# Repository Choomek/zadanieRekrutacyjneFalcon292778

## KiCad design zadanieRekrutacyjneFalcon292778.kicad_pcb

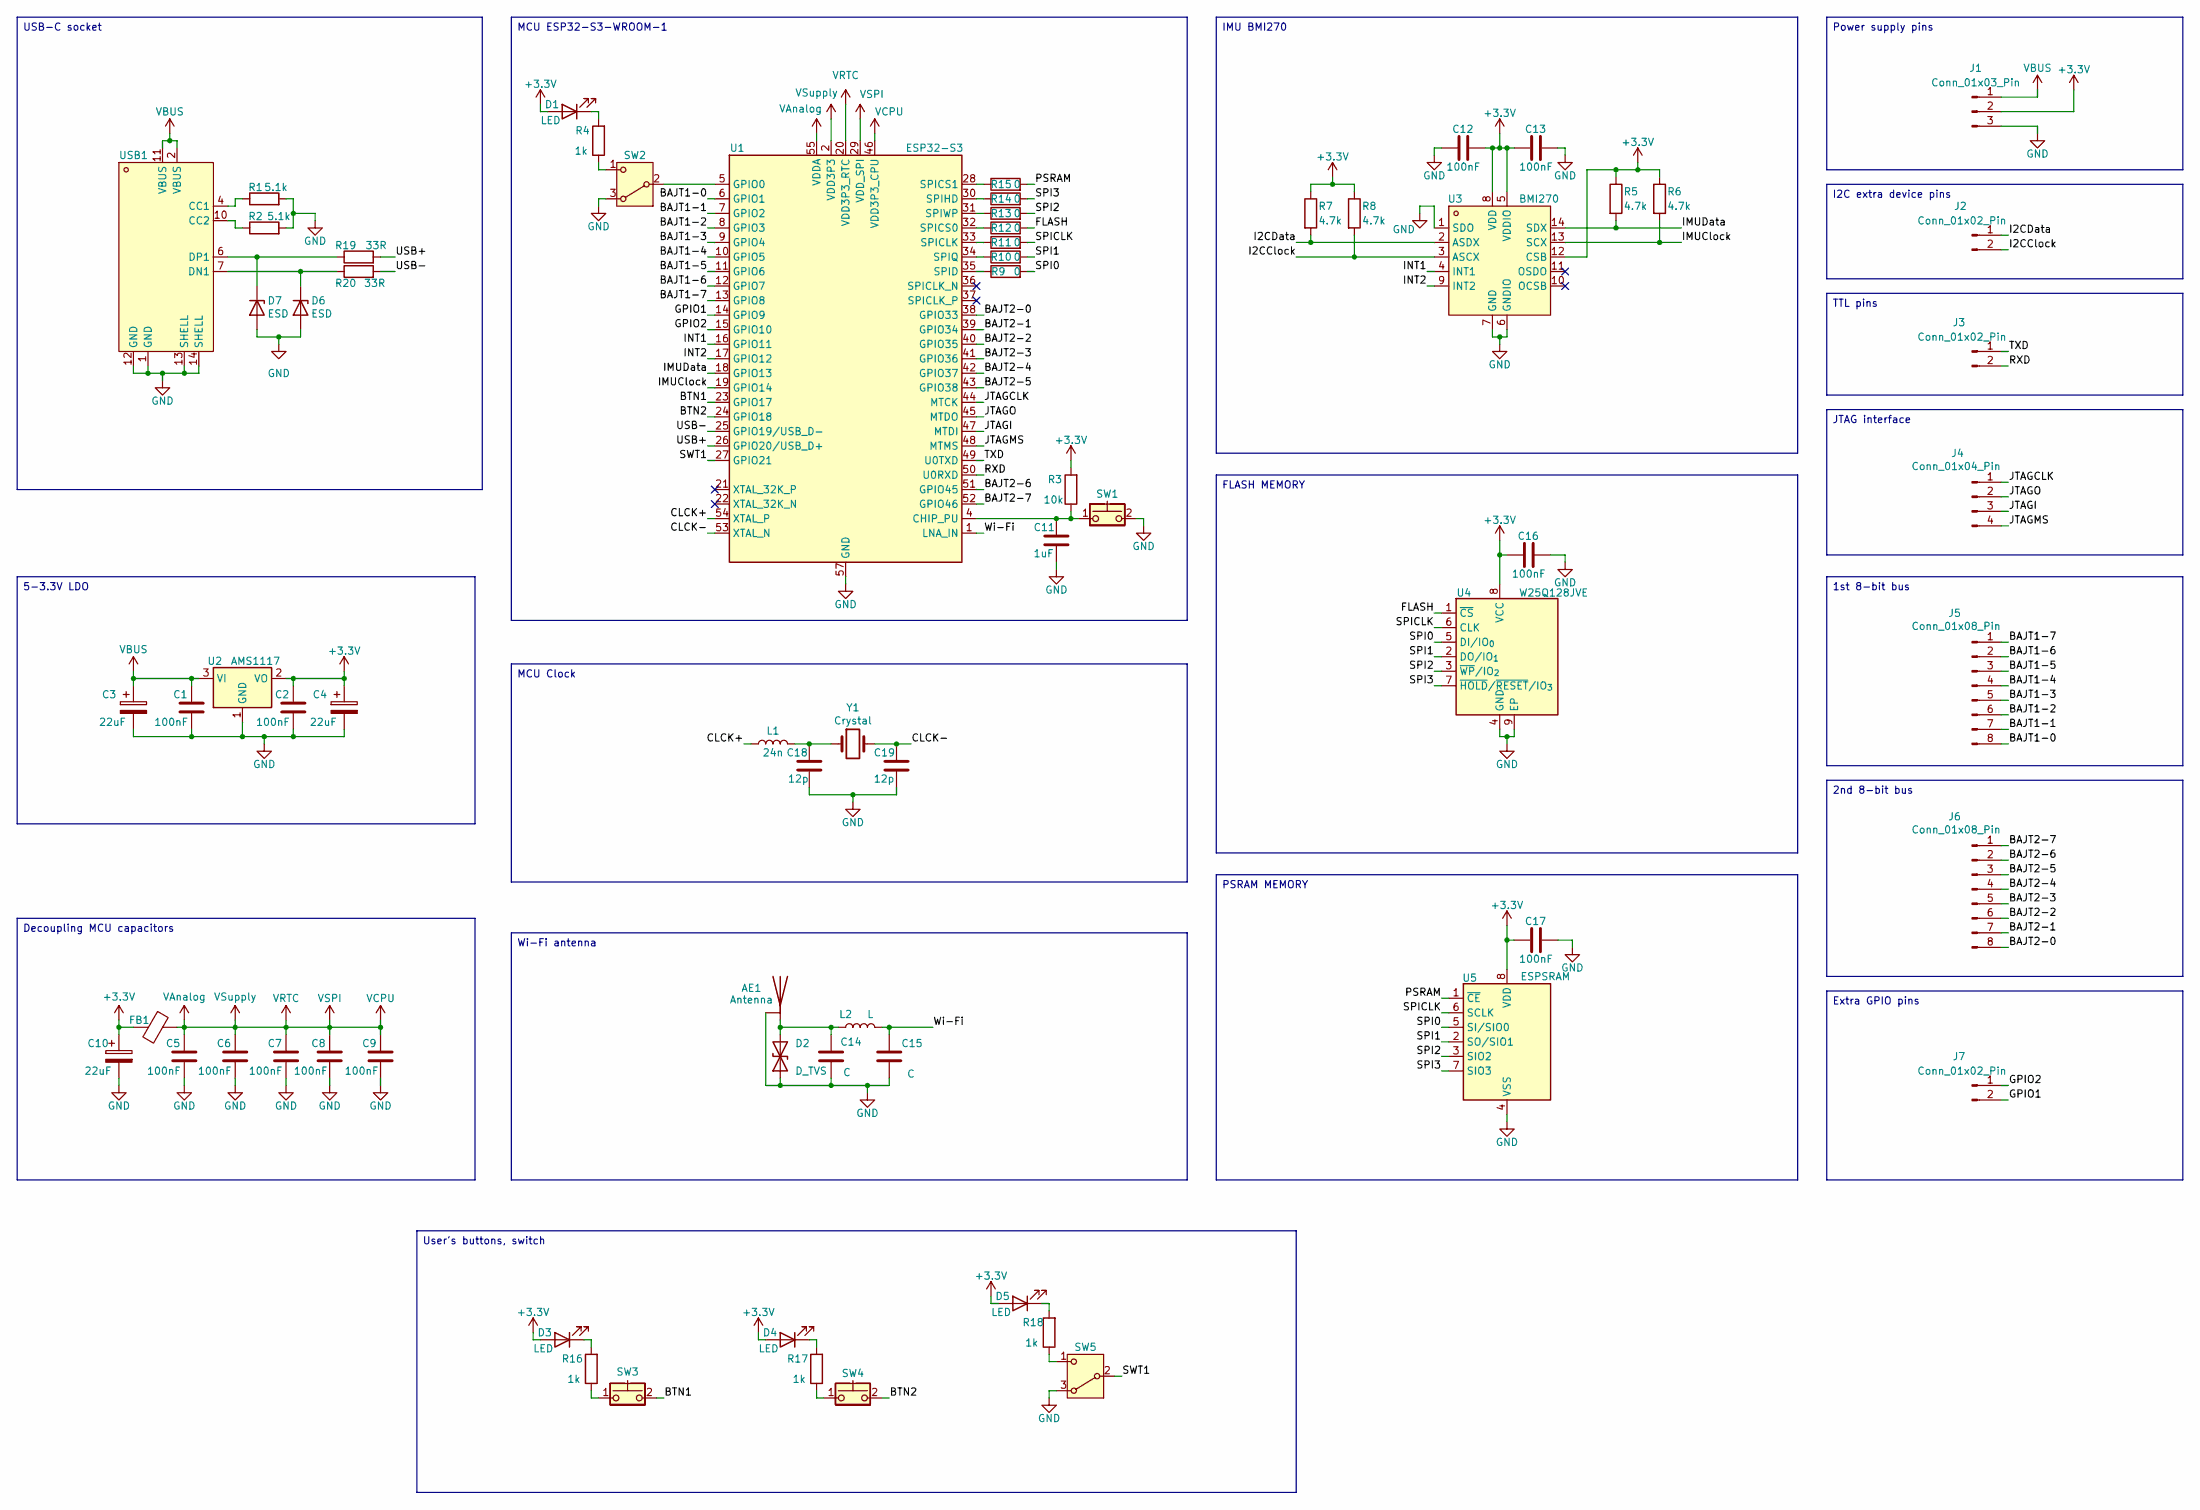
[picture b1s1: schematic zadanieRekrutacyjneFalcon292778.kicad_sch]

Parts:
AE1: Antenna; Texas_SWRA117D_2.4GHz_Right
C1, C2, C5, C6, C7, C8, C9, C12, C13, C16, C17: 100nF; C_0603_1608Metric
C3, C4, C10: 22uF; CP_Axial_L11.0mm_D5.0mm_P18.00mm_Horizontal
C11: 1uF; C_0603_1608Metric
C14, C15: C; C_0603_1608Metric
C18, C19: 12p; C_0603_1608Metric
D1, D3, D4, D5: LED; LED_0603_1608Metric
D2: D_TVS; Texas_DPY0002A_0.6x1mm_P0.65mm
D6, D7: ESD; D_SOD-523
FB1: FerriteBead; LairdTech_28C0236-0JW-10
J1: Conn_01x03_Pin; PinHeader_1x03_P2.54mm_Vertical
J2, J3, J7: Conn_01x02_Pin; PinHeader_1x02_P2.54mm_Vertical
J4: Conn_01x04_Pin; PinHeader_1x04_P2.54mm_Vertical
J5, J6: Conn_01x08_Pin; PinHeader_1x08_P2.54mm_Vertical
L1: 24n; L_0603_1608Metric
L2: L; L_0603_1608Metric
R1, R2: 5.1k; R_0603_1608Metric
R3: 10k; R_0603_1608Metric
R4, R16, R17, R18: 1k; R_0603_1608Metric
R5, R6, R7, R8: 4.7k; R_0603_1608Metric
R9, R10, R11, R12, R13, R14, R15: 0; R_0603_1608Metric
R19, R20: 33R; R_0603_1608Metric
SW1, SW3, SW4: CK_KMS2xxG; SW_SPST_CK_KMS2xxGP
SW2, SW5: SW_Nidec_CAS-120A1; Nidec_Copal_CAS-120A
U1: ESP32-S3; QFN-56-1EP_7x7mm_P0.4mm_EP4x4mm
U2: AMS1117; SOT-223-3_TabPin2
U3: BMI270; LGA-14_L3.0-W2.5-P0.50-BR; LCSC Part C2836813
U4: W25Q128JVE; WSON-8-1EP_8x6mm_P1.27mm_EP3.4x4.3mm
U5: ESPSRAM; SOIC-8_3.9x4.9mm_P1.27mm
USB1: TYPE-C 16PIN 2MD(073); USB-C-SMD_TYPE-C-6PIN-2MD-073; LCSC Part C2765186
Y1: Crystal; Resonator-2Pin_W7.0mm_H2.5mm

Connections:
+3.3V: C2.1, C4.1, C10.1, C12.1, C13.2, C16.2, C17.2, D1.2 (A), D3.2 (A), D4.2 (A), D5.2 (A), FB1.2, J1.2, R3.2, R5.1, R6.1, R7.1, R8.1, U2.2 (VO), U3.5 (VDDIO), U3.8 (VDD), U3.12 (CSB), U4.8 (VCC), U5.8 (VDD)
/BAJT1-0: J5.8, U1.6 (GPIO1)
/BAJT1-1: J5.7, U1.7 (GPIO2)
/BAJT1-2: J5.6, U1.8 (GPIO3)
/BAJT1-3: J5.5, U1.9 (GPIO4)
/BAJT1-4: J5.4, U1.10 (GPIO5)
/BAJT1-5: J5.3, U1.11 (GPIO6)
/BAJT1-6: J5.2, U1.12 (GPIO7)
/BAJT1-7: J5.1, U1.13 (GPIO8)
/BAJT2-0: J6.8, U1.38 (GPIO33)
/BAJT2-1: J6.7, U1.39 (GPIO34)
/BAJT2-2: J6.6, U1.40 (GPIO35)
/BAJT2-3: J6.5, U1.41 (GPIO36)
/BAJT2-4: J6.4, U1.42 (GPIO37)
/BAJT2-5: J6.3, U1.43 (GPIO38)
/BAJT2-6: J6.2, U1.51 (GPIO45)
/BAJT2-7: J6.1, U1.52 (GPIO46)
/BTN1: SW3.2, U1.23 (GPIO17)
/BTN2: SW4.2, U1.24 (GPIO18)
/CLCK+: L1.1, U1.54 (XTAL_P)
/CLCK-: C19.1, U1.53 (XTAL_N), Y1.2
/FLASH: R12.2, U4.1 (~CS)
/GPIO1: J7.2, U1.14 (GPIO9)
/GPIO2: J7.1, U1.15 (GPIO10)
/I2CClock: J2.2, R8.2, U3.3 (ASCX)
/I2CData: J2.1, R7.2, U3.2 (ASDX)
/IMUClock: R6.2, U1.19 (GPIO14), U3.13 (SCX)
/IMUData: R5.2, U1.18 (GPIO13), U3.14 (SDX)
/INT1: U1.16 (GPIO11), U3.4 (INT1)
/INT2: U1.17 (GPIO12), U3.9 (INT2)
/JTAGCLK: J4.1, U1.44 (MTCK)
/JTAGI: J4.3, U1.47 (MTDI)
/JTAGMS: J4.4, U1.48 (MTMS)
/JTAGO: J4.2, U1.45 (MTDO)
/PSRAM: R15.2, U5.1 (~CE)
/RXD: J3.2, U1.50 (U0RXD)
/SPI0: R9.2, U4.5 (DI/IO_{0}), U5.5 (SI/SIO0)
/SPI1: R10.2, U4.2 (DO/IO_{1}), U5.2 (SO/SIO1)
/SPI2: R13.2, U4.3 (~WP/IO_{2}), U5.3 (SIO2)
/SPI3: R14.2, U4.7 (~HOLD/~RESET/IO_{3}), U5.7 (SIO3)
/SPICLK: R11.2, U4.6 (CLK), U5.6 (SCLK)
/SWT1: SW5.2 (B), U1.27 (GPIO21)
/TXD: J3.1, U1.49 (U0TXD)
/USB+: R19.2, U1.26 (GPIO20/USB_D+)
/USB-: R20.2, U1.25 (GPIO19/USB_D-)
/Wi-Fi: C15.1, L2.2, U1.1 (LNA_IN)
GND: AE1.2 (GND), C1.2, C2.2, C3.2, C4.2, C5.2, C6.2, C7.2, C8.2, C9.2, C10.2, C11.2, C12.2, C13.1, C14.2, C15.2, C16.1, C17.1, C18.2, C19.2, D2.1 (A1), D6.2 (A), D7.2 (A), J1.3, R1.2, R2.2, SW1.2, SW2.3 (A), SW5.3 (A), U1.57 (GND), U2.1 (GND), U3.1 (SDO), U3.6 (GNDIO), U3.7 (GND), U4.4 (GND), U4.9 (EP), U5.4 (VSS), USB1.1 (GND), USB1.12 (GND), USB1.13 (SHELL), USB1.14 (SHELL)
unnamed: AE1.1 (A), C14.1, D2.2 (A2), L2.1
unnamed: C18.1, L1.2, Y1.1
unnamed: D1.1 (K), R4.2
unnamed: D3.1 (K), R16.2
unnamed: D4.1 (K), R17.2
unnamed: D5.1 (K), R18.2
unnamed: D6.1 (K), R20.1, USB1.7 (DN1)
unnamed: D7.1 (K), R19.1, USB1.6 (DP1)
unnamed: R16.1, SW3.1
unnamed: R17.1, SW4.1
unnamed: SW2.2 (B), U1.5 (GPIO0)
unnamed: R4.1, SW2.1 (C)
unnamed: R18.1, SW5.1 (C)
unnamed: C11.1, R3.1, SW1.1, U1.4 (CHIP_PU)
unnamed: R11.1, U1.33 (SPICLK)
unnamed: R12.1, U1.32 (SPICS0)
unnamed: R15.1, U1.28 (SPICS1)
unnamed: R9.1, U1.35 (SPID)
unnamed: R14.1, U1.30 (SPIHD)
unnamed: R10.1, U1.34 (SPIQ)
unnamed: R13.1, U1.31 (SPIWP)
unnamed: R1.1, USB1.4 (CC1)
unnamed: R2.1, USB1.10 (CC2)
VAnalog: C5.1, C6.1, C7.1, C8.1, C9.1, FB1.1, U1.2 (VDD3P3), U1.3 (VDD3P3), U1.20 (VDD3P3_RTC), U1.29 (VDD_SPI), U1.46 (VDD3P3_CPU), U1.55 (VDDA), U1.56 (VDDA)
VBUS: C1.1, C3.1, J1.1, U2.3 (VI), USB1.2 (VBUS), USB1.11 (VBUS)

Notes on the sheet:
2nd 8-bit bus
Wi-Fi antenna
IMU BMI270
Decoupling MCU capacitors
USB-C socket
TTL pins
MCU ESP32-S3-WROOM-1
Power supply pins
1st 8-bit bus
PSRAM MEMORY
5-3.3V LDO
FLASH MEMORY
JTAG interface
Extra GPIO pins
User's buttons, switch
I2C extra device pins
MCU Clock

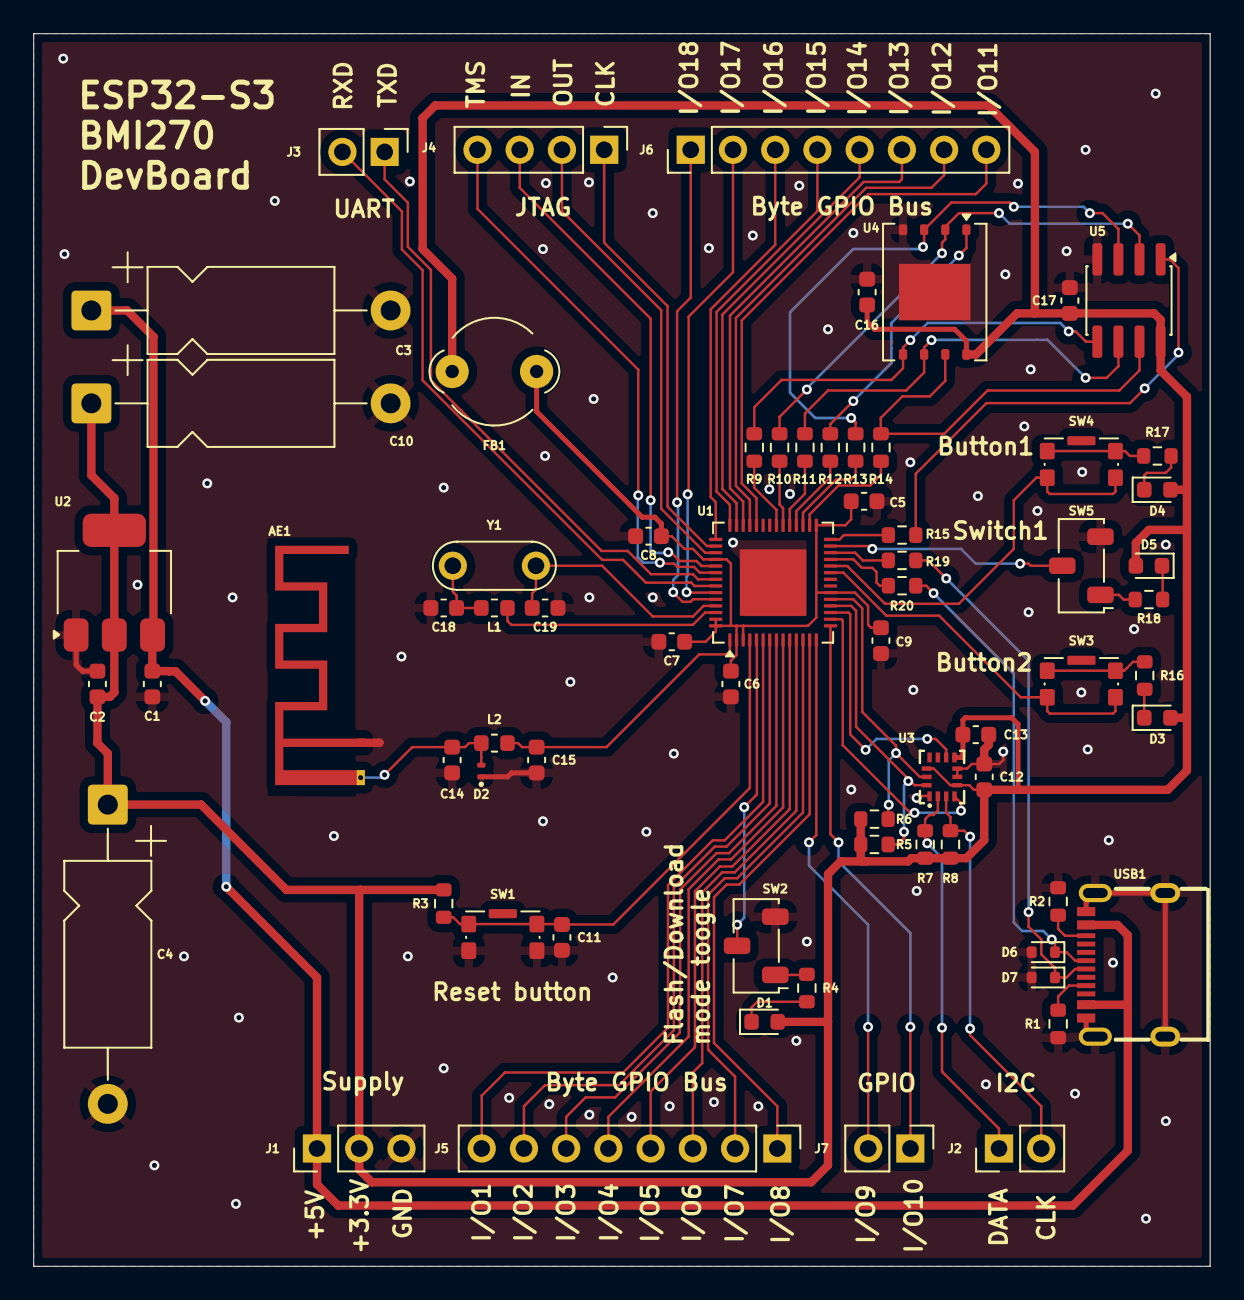
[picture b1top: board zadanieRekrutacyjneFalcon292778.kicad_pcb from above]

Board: 2 copper layers, 70.8 x 74.1 mm, 69 parts (0 on the bottom side), 72 nets.

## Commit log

2026-03-24 schemat + footprinty v1
2026-03-24 schemat + footprinty v2
2026-03-24 placement + testowy tracking v1
2026-03-25 zroutowane (do poprawy footprinty, DRC)
2026-03-27 DRC naprawione 3d modele dodane, transile dodane
2026-03-28 Finalna wersja v1
2026-03-28 Finalna wersja v2 (gerbery)
2026-03-28 Finalna wersja v3
